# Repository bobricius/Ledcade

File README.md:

# Ledcade

Wait please, working on ....

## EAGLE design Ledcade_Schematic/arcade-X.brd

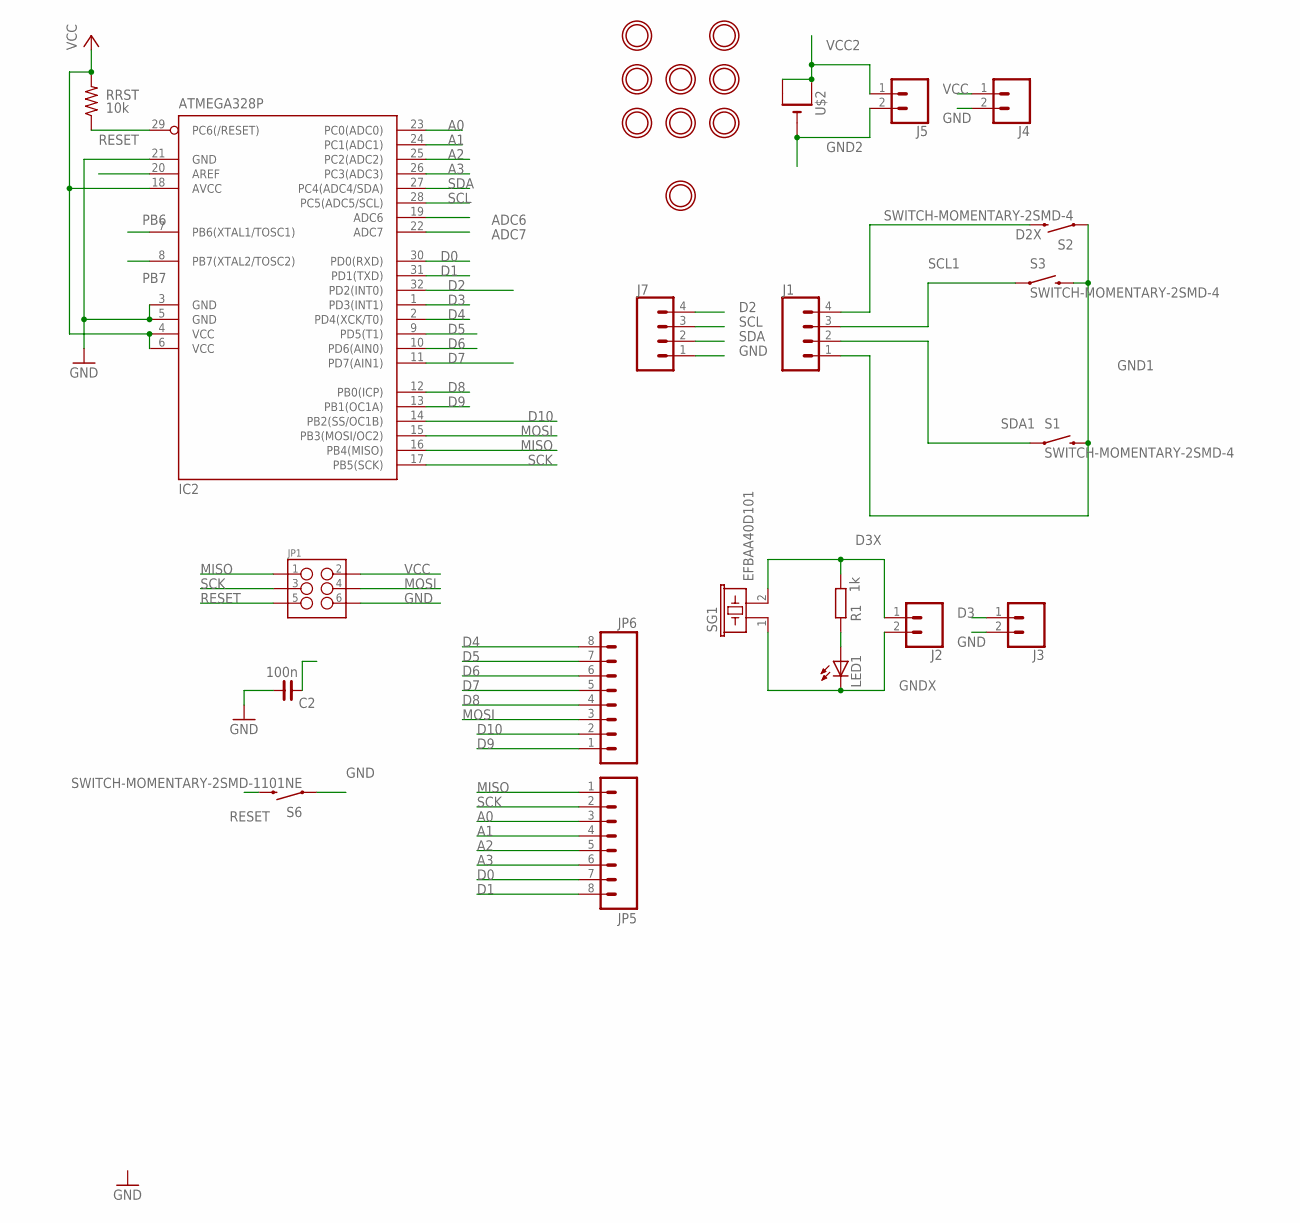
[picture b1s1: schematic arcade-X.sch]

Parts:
C2: 100n; C0805
IC2: ATMEGA328P; TQFP32-08
J1, J7: CONN_04LONGPADS; 1X04_LONGPADS
J2, J3, J4, J5: CONN_02PTH3; 1X02_LONGPADS
JP1: M03X2NO_SILK; 2X3-NS
JP5, JP6: M08NO_SILK; 1X08_PIN1_NO_SILK
LED1: LED3MM
R1: 1k; R0805
RRST: 10k; R0805@1
S1, S2, S3: SWITCH-MOMENTARY-2SMD-4; TACTILE_SWITCH_TALL
S6: SWITCH-MOMENTARY-2SMD-1101NE; TACTILE-SWITCH-1101NE
SG1: EFBAA40D101
U$1: MOUNTINGHOLE3.0THIN; MOUNTINGHOLE_3.0_PLATEDTHIN
U$2: CR2032THM; CR2032-THRU
U$3, U$4, U$5, U$7, U$8, U$9, U$10, U$11: MOUNTINGHOLE2.0; MOUNTINGHOLE_2.0_PLATED

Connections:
A0: IC2.23 (PC0(ADC0)), JP5.3
A1: IC2.24 (PC1(ADC1)), JP5.4
A2: IC2.25 (PC2(ADC2)), JP5.5
A3: IC2.26 (PC3(ADC3)), JP5.6
ADC6: IC2.19 (ADC6)
ADC7: IC2.22 (ADC7)
AREF: IC2.20 (AREF)
D0: IC2.30 (PD0(RXD)), JP5.7
D1: IC2.31 (PD1(TXD)), JP5.8
D2: IC2.32 (PD2(INT0)), J7.4
D2X: J1.4, S2.B2 (2)
D3: IC2.1 (PD3(INT1)), J3.1
D3X: J2.1, R1.1, SG1.2
D4: IC2.2 (PD4(XCK/T0)), JP6.8
D5: IC2.9 (PD5(T1)), JP6.7
D6: IC2.10 (PD6(AIN0)), JP6.6
D7: IC2.11 (PD7(AIN1)), JP6.5
D8: IC2.12 (PB0(ICP)), JP6.4
D9: IC2.13 (PB1(OC1A)), JP6.1
D10: IC2.14 (PB2(SS/OC1B)), JP6.2
GND: C2.1, IC2.3 (GND), IC2.5 (GND), IC2.21 (GND), J3.2, J4.2, J7.1, JP1.6, S6.1
GND1: J1.1, S1.B2 (2), S2.A2 (1), S3.B2 (2)
GND2: J5.2, U$2.-
GNDX: J2.2, LED1.K (C), SG1.1
MISO: IC2.16 (PB4(MISO)), JP1.1, JP5.1
MOSI: IC2.15 (PB3(MOSI/OC2)), JP1.4, JP6.3
unnamed: LED1.A, R1.2
PB6: IC2.7 (PB6(XTAL1/TOSC1))
PB7: IC2.8 (PB7(XTAL2/TOSC2))
RESET: IC2.29 (PC6(/RESET)), JP1.5, RRST.1, S6.2
SCK: IC2.17 (PB5(SCK)), JP1.3, JP5.2
SCL: IC2.28 (PC5(ADC5/SCL)), J7.3
SCL1: J1.3, S3.A2 (1)
SDA: IC2.27 (PC4(ADC4/SDA)), J7.2
SDA1: J1.2, S1.A2 (1)
VCC: C2.2, IC2.4 (VCC), IC2.6 (VCC), IC2.18 (AVCC), J4.1, JP1.2, RRST.2
VCC2: J5.1, U$2.+1 (+), U$2.+2 (+1)

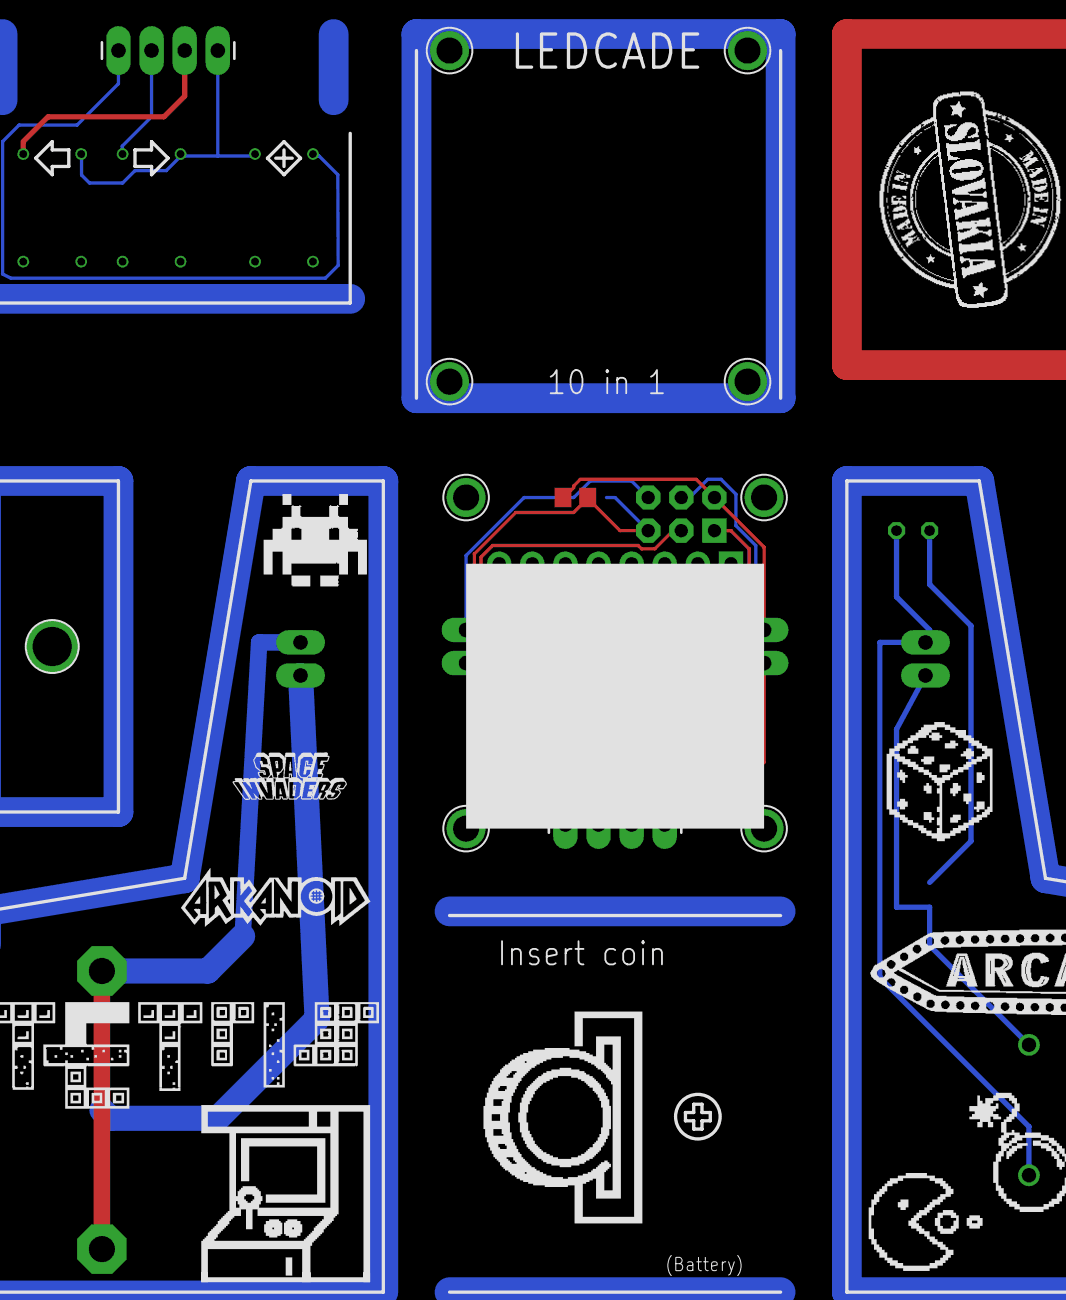
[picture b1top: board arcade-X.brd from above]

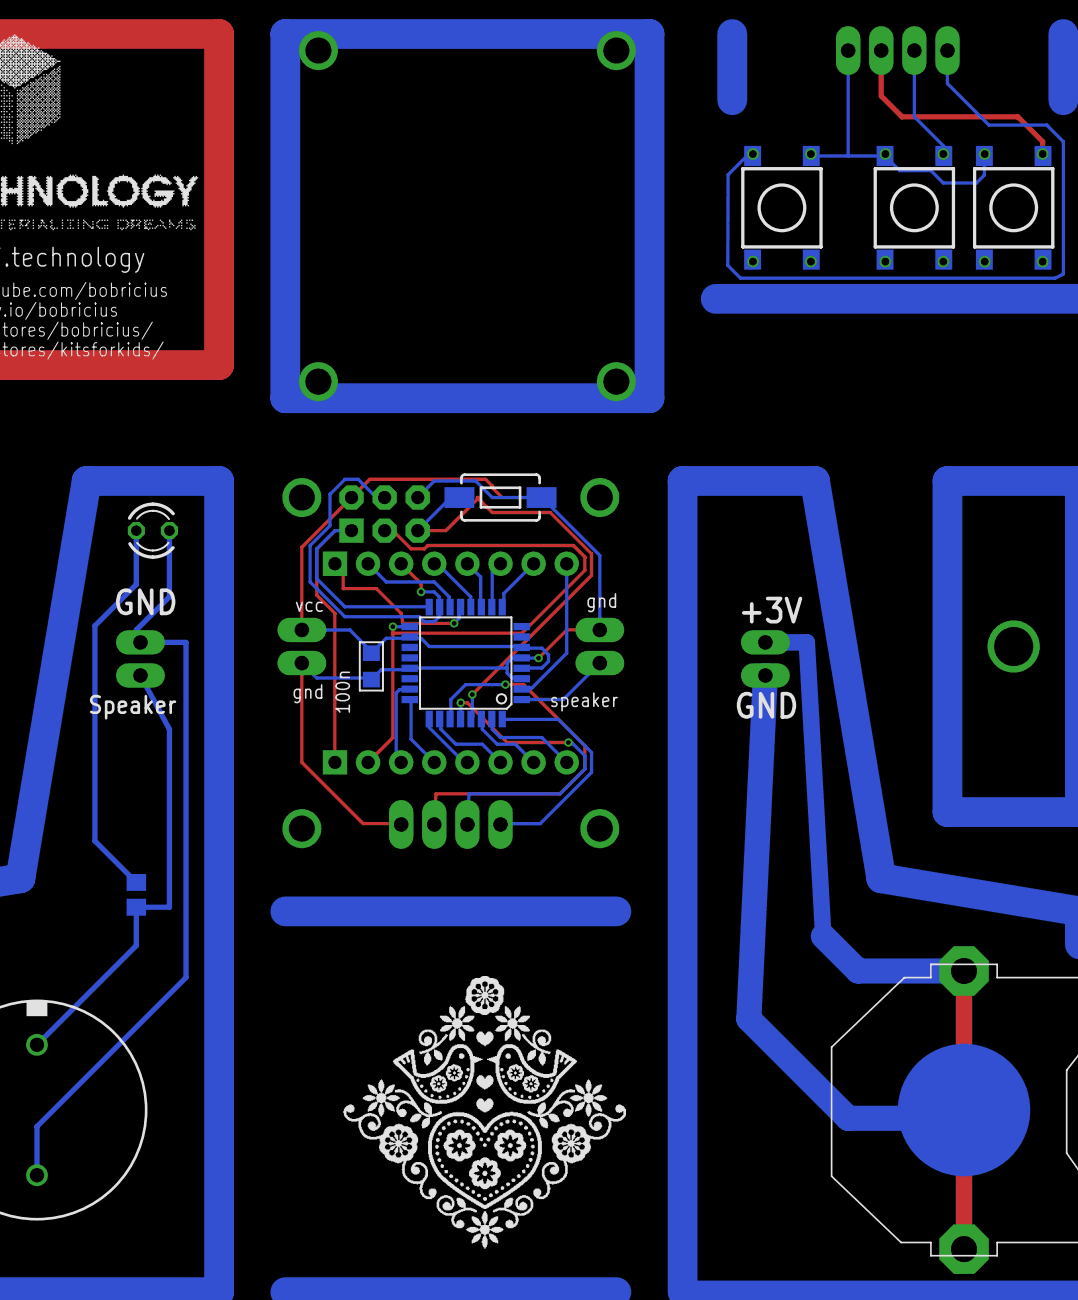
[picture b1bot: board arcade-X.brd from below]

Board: 2 copper layers, 29 parts (12 on the bottom side), 32 nets.

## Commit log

2020-12-25 Add files via upload
    Sources and HEX

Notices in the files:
parts and their libraries:
SparkFun-Electromechanical: Licensing: CC v3.0 Share-Alike You are welcome to use this library for commercial purposes.
